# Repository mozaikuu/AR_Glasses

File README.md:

# Smart Glasses Distilled

This workspace was reorganized into a clean, role-based layout focused on a single Python backend and multiple client integrations.

## Folder Structure

```text
.
├── app/                # Core Python application
│   ├── api/            # HTTP and websocket endpoints
│   ├── agent/          # LLM orchestration and reasoning loop
│   ├── tools/          # Tool integrations (vision/search/navigation/speech)
│   ├── services/       # Runtime services (ASR/TTS/session/routing)
│   ├── models/         # Request/response and domain models
│   ├── config/         # Settings and environment config
│   └── shared/         # Shared helpers
├── bus_system/         # Isolated Smart Bus Tracking MVP workspace
├── clients/            # External client adapters/projects
│   ├── unity/          # Unity/HoloLens integration assets
│   ├── esp32/          # ESP firmware integration notes/assets
│   ├── mobile/         # Mobile client integration
│   └── browser/        # Browser/web integration
├── docs/               # Product and technical documentation
├── scripts/            # Utility scripts for setup/dev/ops
├── tests/              # Automated and smoke tests
├── assets/             # Static assets and models
└── archive/            # Legacy or deprecated snapshots
```

## Startup Contract

- Keep one launcher at project root: `start.py`.
- Core runtime code should live under `app/`.
- Clients should consume APIs only (no direct imports from internal modules).

## Bus System Workspace

All Smart Bus Tracking MVP modules are grouped under `bus_system/` for easier access:

- `bus_system/backend/` API and simulation runtime integration
- `bus_system/frontend/` Next.js dashboard and PWA
- `bus_system/simulation/` route and prediction modules
- `bus_system/agent_tools/` Cerebro tool wrappers
- `bus_system/docs/bus_tracking_mvp/` MVP docs

## Next Move

Place your current backend files under `app/` by responsibility (api/agent/tools/services/etc.), then update imports to use package paths from `app`.

---

Copyright © 2026 Ahmed Moussa

This software is provided to New Mansoura University solely for academic evaluation purposes.

No license, ownership rights, distribution rights, modification rights, or commercial rights are granted.

All intellectual property rights remain with the author.

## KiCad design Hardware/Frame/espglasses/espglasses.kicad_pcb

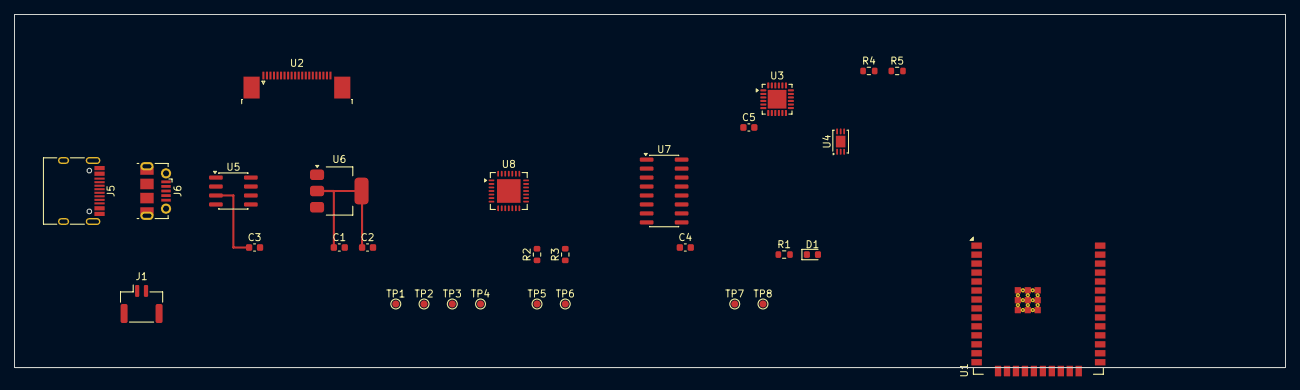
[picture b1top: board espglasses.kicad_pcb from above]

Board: 2 copper layers, 180.0 x 50.0 mm, 30 parts (0 on the bottom side), 15 nets.

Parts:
C1, C3: 10uF; C_0603_1608Metric
C2, C4, C5: 100nF; C_0603_1608Metric
D1: GREEN; LED_0603_1608Metric
J1: BATTERY_1S; JST_GH_SM02B-GHS-TB_1x02-1MP_P1.25mm_Horizontal
J5: USBC_POWER_IN; USB_C_Receptacle_HRO_TYPE-C-31-M-12
J6: MICRO_USB_PROG; USB_Micro-B_Molex-105017-0001
R1: 1k; R_0603_1608Metric
R2, R3, R4, R5: 10k; R_0603_1608Metric
TP1: TP_UART_TX; TestPoint_Pad_D1.0mm
TP2: TP_UART_RX; TestPoint_Pad_D1.0mm
TP3: TP_EN; TestPoint_Pad_D1.0mm
TP4: TP_IO0; TestPoint_Pad_D1.0mm
TP5: TP_I2C_SCL; TestPoint_Pad_D1.0mm
TP6: TP_I2C_SDA; TestPoint_Pad_D1.0mm
TP7: TP_SPK_P; TestPoint_Pad_D1.0mm
TP8: TP_SPK_N; TestPoint_Pad_D1.0mm
U1: ESP32_WROVER_E_CORE; ESP32-WROOM-32E
U2: OV2640_CAMERA_IF; TE_2-1734839-0_1x20-1MP_P0.5mm_Horizontal
U3: MPU6050_CORE; QFN-24-1EP_4x4mm_P0.5mm_EP2.65x2.65mm
U4: INMP441_CORE; DFN-6-1EP_3x2mm_P0.5mm_EP1.65x1.35mm
U5: LIION_CHARGER_IC_CORE; SOIC-8_3.9x4.9mm_P1.27mm
U6: REGULATOR_3V3_CORE; SOT-223-3_TabPin2
U7: AUDIO_AMP_CORE; SOIC-16_3.9x9.9mm_P1.27mm
U8: USB_UART_BRIDGE_CORE; QFN-28-1EP_5x5mm_P0.5mm_EP3.35x3.35mm

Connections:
+3V3_DIG: C1.1, C2.1, R2.1, R3.1, R4.1, R5.1, U1.2, U6.2, U8.9
EN: R4.2, TP3.1, U1.6, U8.7
GND: C1.2, C2.2, C3.2, D1.1, J1.2, J5.A1, J5.A12, J5.B1, J5.B12, J6.5, J6.6, U1.1, U5.4, U6.3, U8.2, U8.10
I2C_SCL: R2.2, TP5.1, U1.32
I2C_SDA: R3.2, TP6.1, U1.34
IO0: R5.2, TP4.1, U1.4, U8.8
LED_A: D1.2, R1.2
LED_STAT: R1.1, U1.8
UART_RX_DBG: TP2.1, U1.12, U8.5
UART_TX_DBG: TP1.1, U1.10, U8.6
USB_PROG_D+: J6.3, U8.3
USB_PROG_D-: J6.2, U8.4
VBAT_RAW: J1.1, U5.2
VBUS_5V: J5.A4, J5.A9, J5.B4, J5.B9, J6.1, U5.1, U8.1
VSYS: C3.1, U5.3, U6.1

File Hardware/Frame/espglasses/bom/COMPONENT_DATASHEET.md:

# Component Datasheet (Initial Concrete Set)

This file is generated from the concrete purchased-part implementation model.
Entries are the individual component-level building blocks for Rev-B decomposition.

| Ref | Part | Package | Role | Rail/Signal | Notes |
|---|---|---|---|---|---|
| U1 | ESP32-WROVER-E | Module | Main MCU + Wi-Fi/BLE | +3V3_DIG | Camera-capable ESP32 core |
| U2 | OV2640 | Camera sensor module/FFC | Image sensor | CAM_* | Parallel camera interface block |
| U3 | MPU-6050 | QFN (module-equivalent support) | 6-axis IMU | I2C_* | I2C sensor |
| U4 | INMP441 | LGA | Digital MEMS microphone | I2S_* | I2S microphone |
| U5 | Li-ion charger IC (Type-C input) | SOP/QFN | Battery charging | VBUS_5V/VBAT_RAW | Equivalent of purchased Type-C charger board |
| U6 | 3.3V regulator IC | SOT-223/SOT-23-5 | System regulation | VSYS/+3V3_DIG | Equivalent of purchased regulator stage |
| U7 | Audio amplifier IC | SOP/QFN | Speaker drive | AUD_IN/SPK_OUT | For 8 ohm 0.5W speaker |
| J1 | Li-ion battery connector | 2-pin JST | Battery input | VBAT_RAW | 3.7V 1000mAh battery |
| J2 | OLED panel connector | 4-pin header/FFC | Display interface | I2C_SCL/I2C_SDA | 1.3 inch I2C OLED |
| J3 | Camera connector | FFC/header | Camera link | CAM_* | OV2640 connection |
| J4 | Speaker connector | 2-pin | Audio transducer output | SPK_OUT | 20mm 8 ohm speaker |
| J5 | UART/boot header | 1x6 2.54mm | Debug/programming | UART/EN/IO0 | Bring-up and flashing |
| D1 | Status LED | 0603 | Power/status indication | LED_STAT | User-visible status |
| R1 | 1k | 0603 | LED current limit | LED_STAT | Status LED resistor |
| R2 | 10k | 0603 | I2C pull-up | I2C_SCL | Bus pull-up |
| R3 | 10k | 0603 | I2C pull-up | I2C_SDA | Bus pull-up |
| R4 | 10k | 0603 | EN pull-up | EN | ESP32 enable strap |
| R5 | 10k | 0603 | IO0 pull-up | IO0 | ESP32 boot strap |
| C1 | 10uF | 0603/0805 | Bulk decoupling | +3V3_DIG | Near ESP32/regulator |
| C2 | 100nF | 0603 | HF decoupling | +3V3_DIG | Near ESP32 power pins |
| C3 | 10uF | 0603/0805 | Regulator output bulk | +3V3_DIG | Regulator stability |
| C4 | 100nF | 0603 | Mic decoupling | +3V3_AUD | Near INMP441 |
| C5 | 100nF | 0603 | IMU decoupling | +3V3_DIG | Near MPU-6050 |
| X1 | HW-104 (exact variant pending) | Unknown | Unresolved purchased module | TBD | Needs exact module identification before schematic lock |

## Notes

- HW-104 is intentionally marked unresolved until exact module function is confirmed.
- Final manufacturer part numbers and exact footprints should be locked before fabrication.
- This file is intended to be updated as schematic references are finalized.

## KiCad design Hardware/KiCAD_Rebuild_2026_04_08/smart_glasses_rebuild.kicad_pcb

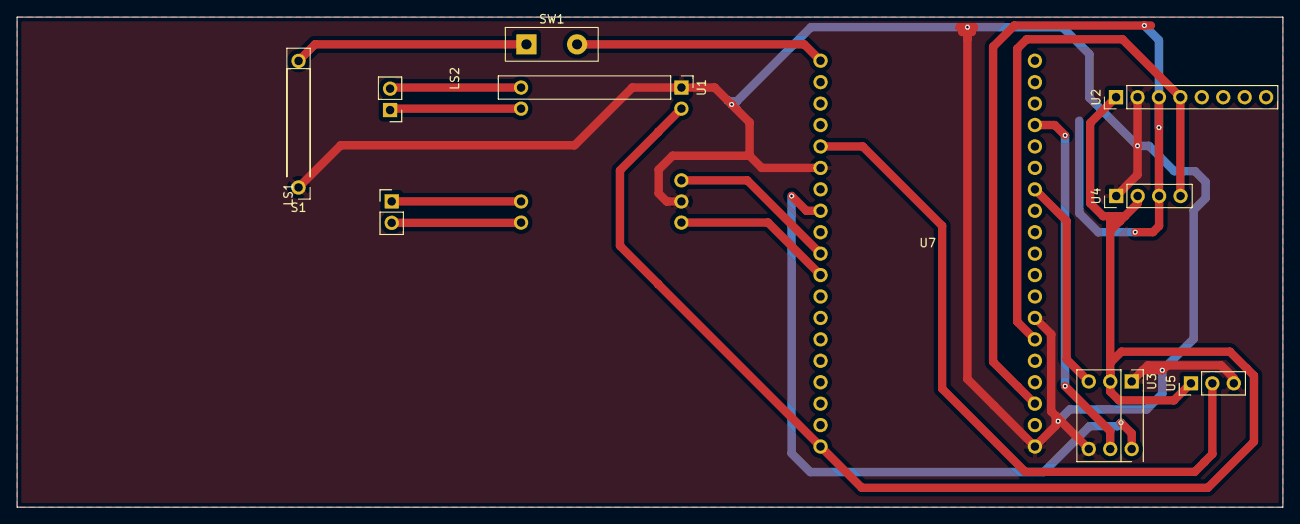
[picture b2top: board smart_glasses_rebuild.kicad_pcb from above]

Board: 2 copper layers, 150.0 x 58.1 mm, 10 parts (0 on the bottom side), 16 nets.

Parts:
LS1, LS2: Small Speaker; PinHeader_1x02_P2.54mm_Vertical
S1: TP4056_BMS; PinHeader_1x06_P2.54mm_Vertical
SW1: PWR_SW_LATCH; Power_Switch_Latching_SPST_2Pin
U1: HW-104; PinHeader_1x09_P2.54mm_Vertical
U2: MPU-6050_Breakout; PinHeader_1x08_P2.54mm_Vertical
U3: INMP441; PinHeader_1x06_P2.54mm_Vertical
U4: IIC_OLED; PinHeader_1x04_P2.54mm_Vertical
U5: HW-763; PinHeader_1x03_P2.54mm_Vertical
U7: ESP32-WROVER-dev; ESP32_WROVER_DEV_2x19_WIDE

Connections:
GND: S1.6 (OUT-), U1.1 (GND), U1.4 (SIG_GND), U2.2 (GND), U3.1 (GND), U3.6 (L/R), U4.1 (GND), U5.3 (GND), U7.14 (GND), U7.20 (GND), U7.26 (GND)
unnamed: LS1.1 (+), U1.8 (R+)
unnamed: LS1.2 (-), U1.9 (R-)
unnamed: LS2.1 (+), U1.6 (L+)
unnamed: LS2.2 (-), U1.7 (L-)
unnamed: S1.5 (OUT+), SW1.1
unnamed: U1.5 (LIN), U7.9 (GPIO25)
unnamed: U1.3 (RIN), U7.10 (GPIO26)
unnamed: U1.2 (VCC), U2.1 (VCC), U3.2 (VDD), U4.2 (VCC), U5.1 (VCC), U7.1 (3V3)
unnamed: U2.3 (SCL), U4.3 (SCL), U7.22 (GPIO22)
unnamed: U2.4 (SDA), U4.4 (SDA), U7.25 (GPIO21)
unnamed: U3.4 (SCK), U7.12 (GPIO14)
unnamed: U3.3 (SD), U7.32 (GPIO4)
unnamed: U3.5 (WS), U7.35 (GPIO15)
unnamed: U5.2 (SIG), U7.15 (GPIO13)
unnamed: SW1.2, U7.19 (5V)

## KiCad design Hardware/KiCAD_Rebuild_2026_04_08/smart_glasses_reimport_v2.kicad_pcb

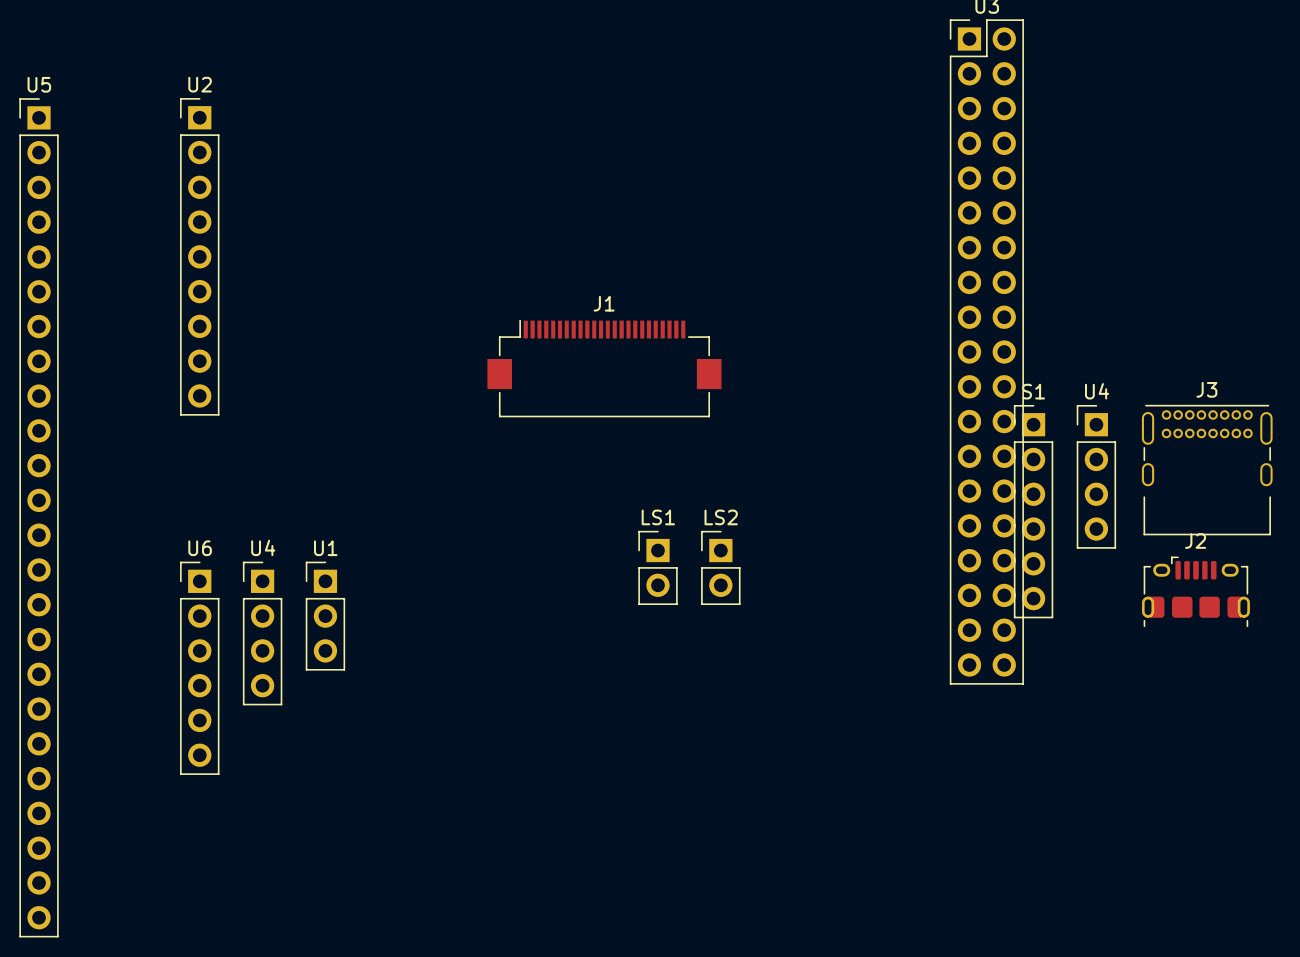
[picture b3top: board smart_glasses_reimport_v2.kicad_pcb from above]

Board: 2 copper layers, 13 parts (0 on the bottom side), 7 nets, no tracks yet.

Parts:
J1: OV2640_STRIP_CONN; Hirose_FH12-24S-0.5SH_1x24-1MP_P0.50mm_Horizontal
J2: DEBUG_USB_MICRO; USB_Micro-B_Amphenol_10118194_Horizontal
J3: CHARGE_USB_C; USB_C_Receptacle_GCT_USB4085
LS1, LS2: Small Speaker; PinHeader_1x02_P2.54mm_Vertical
S1: TP4056_BMS; PinHeader_1x06_P2.54mm_Vertical
U1: HW-763; PinHeader_1x03_P2.54mm_Vertical
U2: HW-104; PinHeader_1x09_P2.54mm_Vertical
U3: ESP32-WROVER-dev; PinHeader_2x19_P2.54mm_Vertical
U4: IIC OLED; PinHeader_1x04_P2.54mm_Vertical
U4#2: HW-764_5V_to_3V3; PinHeader_1x04_P2.54mm_Vertical
U5: OV2640; PinHeader_1x24_P2.54mm_Vertical
U6: INMP441; PinHeader_1x06_P2.54mm_Vertical

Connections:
/CAM_1: J2.5 (GND), U1.2 (GND), U2.5 (SIG_GND), U3.6 (GPIO35), U3.32 (GPIO4), U3.38 (SD_CLK/GPIO6), U4.2 (GND), U4#2.2 (IN-), U4#2.4 (OUT-), U6.4 (WS)
/CAM_8: U3.33 (GPIO0), U4.4 (SDA)
/CAM_12: J1.12 (Y4), U3.17 (SD_DATA_3/GPIO10)
/CAM_16: U3.26 (GND), U6.5 (SD)
/MIC_WS: U3.23 (U0TXD/GPIO1), U6.6 (L/R)
/SPK_RN: LS2.1 (+), U2.9 (R-)
/TOUCH_SIG: U1.3 (SIG), U3.5 (GPIO34)

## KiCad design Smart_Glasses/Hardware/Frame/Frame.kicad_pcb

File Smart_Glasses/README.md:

# Smart Glasses Project

Your AI companion and navigation in Smart Glasses - A multimodal LLM agent with vision, voice, and text capabilities.

## Repo Index

See `docs/PROJECT_INDEX.md` for a map of all sub-projects in this monorepo (Python agent/UI/server, Unity HoloLens project, firmware, mobile, and prototypes).

## Project Structure

The project follows a domain-driven architecture:

```
Smart_Glasses/
├── ui/                    # Streamlit frontend
│   ├── app.py            # Main Streamlit app
│   ├── components/       # UI components
│   └── utils/            # UI utilities
├── agent/                # LLM agent logic
│   ├── llm.py           # LLM model handling & generation
│   ├── agent_loop.py    # Main agent reasoning loop
│   └── modes.py         # Quick/thinking mode logic
├── tools/                # MCP tools
│   ├── vision/          # Computer vision tools (YOLO)
│   ├── search/          # Web search tools
│   ├── speech/          # Speech recognition & TTS
│   └── navigation/      # GPS/navigation tools
├── server/               # MCP server
│   ├── server.py        # FastMCP server definition
│   └── gateway.py       # HTTP gateway for Streamlit
├── models/               # Data models
│   └── requests.py      # Pydantic models for API
├── config/               # Configuration
│   ├── settings.py      # App settings
│   └── model_config.py  # LLM model configuration
└── shared/               # Shared utilities
    └── utils.py         # Common utilities
```

## Features

-  **Multimodal Input**: Support for text, voice, and image inputs
-  **Two Agent Modes**:
   -  **Quick Mode**: Fast single-pass responses
   -  **Thinking Mode**: Deep reasoning with history looping until satisfied
-  **MCP Tools**:
   -  `VisionDetect`: Real-time object detection using camera and YOLO model
   -  `search_web`: Web search and context retrieval
-  **Streamlit UI**: Interactive web interface with live camera and audio capture

## Quickstart

### 1. Install Dependencies

**Important**: You must install dependencies before running the application!

**Option A: Using `uv` (Recommended)**

```bash
uv sync
```

**Option B: Using `pip`**

```bash
pip install -r requirements.txt
```

### 2. Activate Virtual Environment

**Windows:**

```bash
.venv\Scripts\activate
```

**Linux/Mac:**

```bash
source .venv/bin/activate
```

### 3. Start the HTTP Gateway

**Open a terminal** (with venv activated) and run:

**Windows (using batch file):**

```bash
start_gateway.bat
```

**Linux/Mac (using shell script):**

```bash
chmod +x start_gateway.sh
./start_gateway.sh
```

**Or manually:**

```bash
python start_gateway.py
```

You should see:

```
🚀 Starting gateway server on localhost:8000
INFO:     Uvicorn running on http://localhost:8000
```

**⚠️ Keep this terminal open!** The gateway must be running for the Streamlit app to work.

The gateway will be available at `http://localhost:8000`

### 4. Start the Streamlit App

**Open a NEW terminal**, activate the virtual environment, and run:

**Windows (using batch file):**

```bash
start_streamlit.bat
```

**Linux/Mac (using shell script):**

```bash
chmod +x start_streamlit.sh
./start_streamlit.sh
```

**Or manually:**

```bash
# Activate venv first
streamlit run ui/app.py
```

The app will open in your browser at `http://localhost:8501`

### Troubleshooting

**"ModuleNotFoundError" or "No module named 'fastapi'"**

-  Solution: Install dependencies first with `uv sync` or `pip install -r requirements.txt`

**"Connection refused" or "Gateway Offline"**

-  Solution: Make sure the gateway server is running (Step 2). Check that you see the startup message in the gateway terminal.

See `QUICKSTART.md` for more detailed troubleshooting.

## Usage

1. **Text Input**: Type your question in the text area
2. **Image Input**: Click "Capture Frame" to capture the current camera frame
3. **Voice Input**: Click "Capture Audio" to capture audio from your microphone
4. **Send Request**: Click "Send Request" to process all inputs together
5. **Mode Selection**: Choose between "quick" (fast) or "thinking" (deep reasoning) mode

The agent will:

-  Transcribe audio if provided
-  Combine text + transcribed audio + image into a unified prompt
-  Process through the LLM agent with available MCP tools
-  Return a response

## Configuration

Edit `config/settings.py` or set environment variables:

-  `MODEL_ID`: LLM model identifier (default: "google/gemma-3-4b-it")
-  `DEVICE`: "cuda" or "cpu" (default: auto-detected)
-  `API_HOST`: Gateway host (default: "localhost")
-  `API_PORT`: Gateway port (default: 8000)
-  `MAX_LOOPS`: Maximum agent loop iterations (default: 8)

## MCP Server

The MCP server can be used independently with Claude Desktop or other MCP clients.

### Claude Desktop Configuration

On Windows: `%APPDATA%/Claude/claude_desktop_config.json`

```json
{
	"mcpServers": {
		"smart-glasses": {
			"command": "uv",
			"args": [
				"--directory",
				"D:\\0_code\\New_ideas\\1_Coding_Now\\Smart_Glasses",
				"run",
				"fastmcp",
				"run",
				"server.server:mcp",
				"--transport",
				"stdio"
			]
		}
	}
}
```

### Debugging with MCP Inspector

```bash
npx @modelcontextprotocol/inspector uv --directory D:\0_code\New_ideas\1_Coding_Now\Smart_Glasses run fastmcp run server.server:mcp --transport stdio
```

## Development

### Project Scripts

-  `start_gateway.py`: Start the HTTP gateway server
-  `server/server.py`: MCP server entry point
-  `ui/app.py`: Streamlit application

### Testing

Test the end-to-end flow:

1. Start the gateway
2. Start the Streamlit app
3. Try different input combinations (text, image, audio)
4. Test both quick and thinking modes
5. Verify MCP tool calls work (vision detection, web search)

## Migration Notes

See `MIGRATION_NOTES.md` for details about the refactoring from the old structure.

## Dependencies

Key dependencies:

-  `fastmcp`: MCP server framework
-  `streamlit`: Web UI framework
-  `streamlit-webrtc`: WebRTC for camera/audio
-  `transformers`: LLM models
-  `torch`: Deep learning framework
-  `ultralytics`: YOLO object detection
-  `whisper`: Speech recognition
-  `edge-tts`: Text-to-speech
-  `fastapi`: HTTP API framework

See `pyproject.toml` for the complete list.

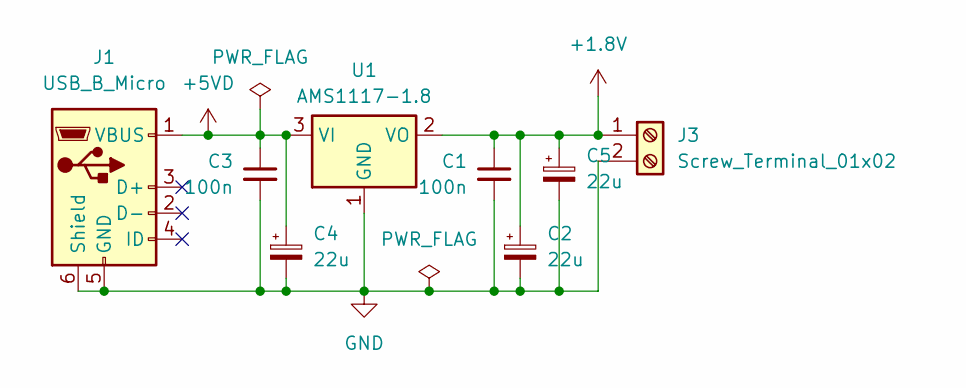
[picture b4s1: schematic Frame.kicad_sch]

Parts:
C1, C3: 100n; C_0402_1005Metric
C2, C4, C5: 22u; CP_Elec_6.3x7.7
J1: USB_B_Micro; USB_Micro-B_Amphenol_10118194_Horizontal
J3: Screw_Terminal_01x02; TerminalBlock_Phoenix_MKDS-1,5-2-5.08_1x02_P5.08mm_Horizont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
U1: AMS1117-1.8; SOT-223-3_TabPin2

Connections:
+1.8V: C1.1, C2.1, C5.1, J3.1, U1.2 (VO)
+5VD: C3.1, C4.1, J1.1 (VBUS), U1.3 (VI)
GND: C1.2, C2.2, C3.2, C4.2, C5.2, J1.5 (GND), J1.6 (Shield), J3.2, U1.1 (GND)

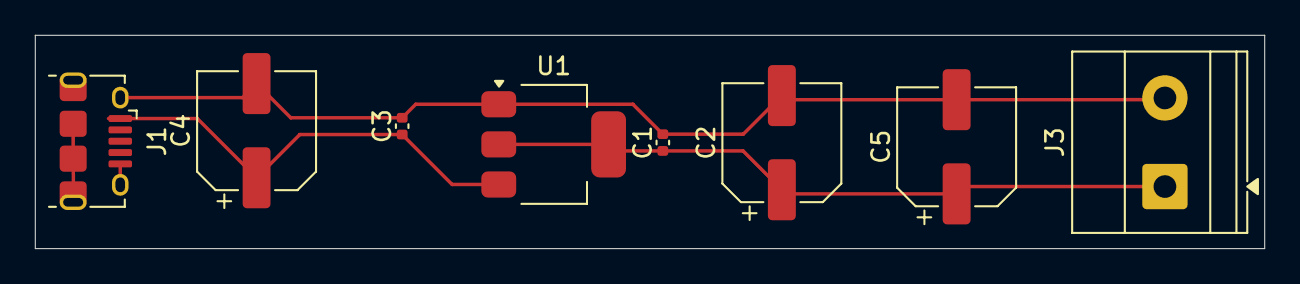
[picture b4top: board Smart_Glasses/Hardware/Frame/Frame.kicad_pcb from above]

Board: 2 copper layers, 70.5 x 12.2 mm, 8 parts (0 on the bottom side), 3 nets.

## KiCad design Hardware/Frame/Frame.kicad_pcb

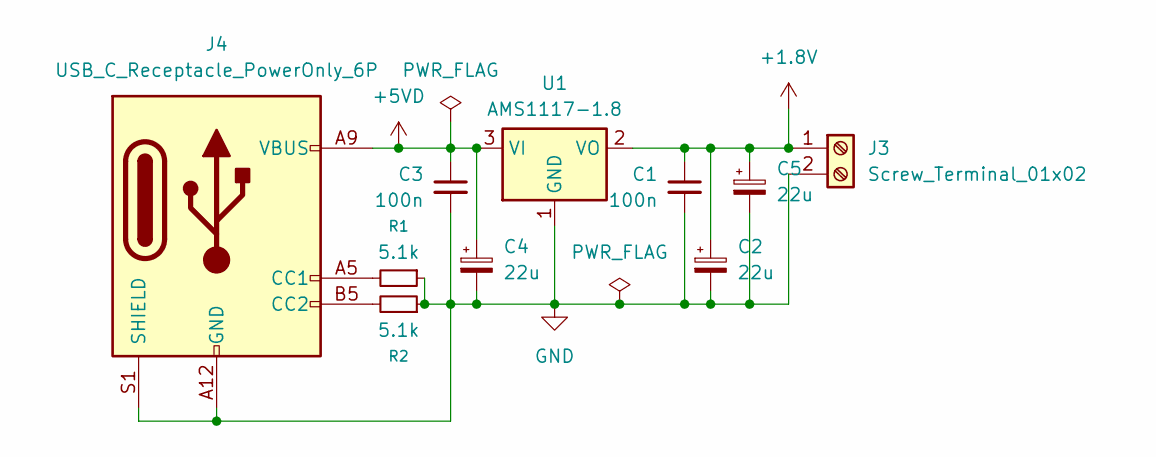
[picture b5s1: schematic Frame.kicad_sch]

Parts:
C1, C3: 100n; C_0402_1005Metric
C2, C4, C5: 22u; CP_Elec_6.3x7.7
J3: Screw_Terminal_01x02; TerminalBlock_Phoenix_MKDS-1,5-2-5.08_1x02_P5.08mm_Horizont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
J4: USB_C_Receptacle_PowerOnly_6P; USB_C_Receptacle_HRO_TYPE-C-31-M-12
R1, R2: 5.1k; R_0402_1005Metric
U1: AMS1117-1.8; SOT-223-3_TabPin2

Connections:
+1.8V: C1.1, C2.1, C5.1, J3.1, U1.2 (VO)
+5VD: C3.1, C4.1, J4.A9 (VBUS), J4.B9 (VBUS), U1.3 (VI)
GND: C1.2, C2.2, C3.2, C4.2, C5.2, J3.2, J4.A12 (GND), J4.B12 (GND), J4.S1 (SHIELD), R1.1, R2.1, U1.1 (GND)
unnamed: J4.A5 (CC1), R1.2
unnamed: J4.B5 (CC2), R2.2

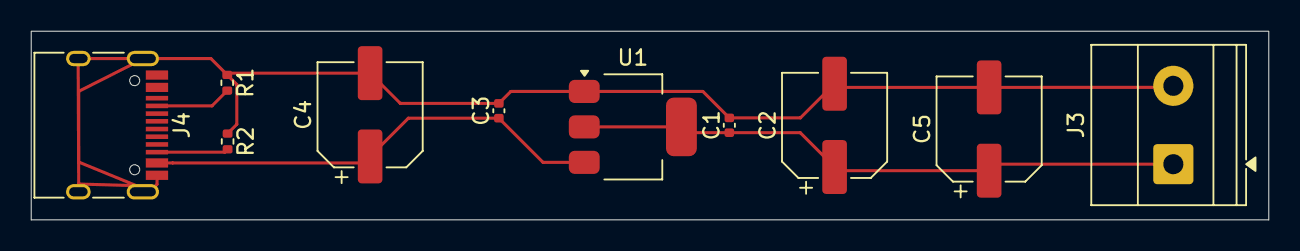
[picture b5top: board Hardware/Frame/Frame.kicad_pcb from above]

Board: 2 copper layers, 80.2 x 12.2 mm, 10 parts (0 on the bottom side), 5 nets.

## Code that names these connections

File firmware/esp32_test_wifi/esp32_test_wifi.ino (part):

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#define PROFILE_USE_TOUCH 1
#else
// Camera-priority default profile:
// WROVER camera pin map overlaps with SH1106 I2C (GPIO21/22) and DAC TTS (GPIO25/26).
// Camera D0 also uses GPIO4, which conflicts with the I2S mic data pin.
// Keep camera enabled and disable conflicting peripherals in the default profile.
#define PROFILE_USE_SH1106 0
#define PROFILE_USE_DAC_TTS 0
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#else
#define TOUCH_PAD_PIN 18
#endif
#define I2C_SDA_PIN 21
#define I2C_SCL_PIN 22
#define I2S_MIC_BCK 14
#define I2S_MIC_WS 15
#define I2S_MIC_DATA 4
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
#if USE_TOUCH
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#error "TOUCH_PAD_PIN conflicts with camera pins. Move touch OUT to a camera-safe GPIO (e.g. GPIO13)."
#endif
#endif
#endif
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  pinMode(DAC_TTS_LEFT_PIN, OUTPUT);
  pinMode(DAC_TTS_RIGHT_PIN, OUTPUT);
  writeDacPair(128);
  Serial.println("TTS DAC init on GPIO25/26");
}

bool playWavFromHttp(HTTPClient &http)
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  i2s_zero_dma_buffer(I2S_NUM_0);
  micDriverInstalled = true;
  micReady = true;
  Serial.println("I2S mic ready (GPIO14/15/4)");
#else
  micReady = false;
#endif
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  pinMode(TOUCH_PAD_PIN, INPUT_PULLDOWN);
#endif
#if USE_SH1106
  Wire.begin(I2C_SDA_PIN, I2C_SCL_PIN);
#endif

#if USE_SH1106
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
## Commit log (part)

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2025-10-15 Init Unity Template
2025-10-15 Init Unity Start Ready
2025-10-16 Surprise update
2025-10-16 mouse movement
2025-10-17 exit btn
2025-10-18 Collision detection
2025-10-20 addtional edits
2025-10-20 test
2025-10-20 menu esc
2025-10-22 sounds&url
2025-10-22 flasks import with collision
2025-10-23 Misc
2025-10-23 Hard_Reset
2025-10-23 Both_input_Systems
2025-10-24 Fixing Version Control
2025-10-24 new collision test
2025-10-24 added Other Scenes
2025-10-24 FIxed Some Errors
2025-10-28 reactions
2025-11-07 Adding ClassElement
2025-11-18 Change Of Plans...
2025-11-18 TTP Done. for now
2025-11-19 Better test case and file structure
2025-11-20 BMC + Comp_analysis + Presentation
2025-11-21 An attempt at GPS facing position without the needed modules
2025-12-01 Added Documentation stuff+ Project vision + GPS
2025-12-01 VC Fix
2025-12-01 Test GPS Done
2025-12-02 Panic at the disco
2025-12-02 Changed folder structur to start MCP Server
2025-12-02 MCP WIP
2025-12-03 Folder Restructure... again
2025-12-20 lots of stuff mainly client llm server stuff. kept forgetting to push so consider this a snapshot with alot of changes in physical files inside (old) plus other updates known to work separately. bad 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
2025-12-20 latest and greatest
2025-12-26 broken stuff but a snapshot none the less
2026-01-08 Audio works now. the start of vibe coding and i hate it
2026-01-11 nova wake up
2026-01-11 Nova + gui
2026-01-16 prep next task
2026-01-16 Fix Version Control
2026-01-16 Team meeting
2026-01-16 move repo + todo upd
2026-01-16 req fix
2026-01-16 streamlit online fix?
2026-01-16 streamlit misbehavior
2026-01-17 sl hotfix
2026-01-20 presentation prep
2026-01-27 updated and cleaned todo + might add moltbot to the repo.
2026-01-28 added 3 month plan in todo
2026-01-28 Nav start
2026-01-30 Claude Code Massacre
2026-01-30 nav integrated
2026-02-01 broken
2026-02-01 Todo to see how gh works
2026-02-01 Rapture + fix code
2026-02-01 requirements?
2026-02-01 fixed mot errors
2026-02-01 build: replace ddgs with duckduckgo-search package
    Update pyproject.toml and check_dependencies.py to use the duckduckgo-search package instead of ddgs. This change aligns with the package naming used in the import statements and ensures consistency 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
2026-02-02 feat(wakeword): add pause/resume and device selection
    - Add pause() and resume() methods to temporarily stop/restart wake word detection
    - Add device_index parameter to allow specifying audio input device
    - Implement auto-refresh loop in Streamlit app for background event processing
    - Add audio device discovery function to find valid input devices
    - Ensure wake word system resumes after manual audio recording
2026-02-02 Streamlit -> Flask
2026-02-02 wakeword fixed
2026-02-02 feat(services): auto-start wake word listening and improve vision tool
    - WakeWordService now automatically starts listening on initialization
    - Update vision model path and add automatic download fallback
    - Expand vision tool trigger phrases for more natural queries
    - Fix camera error message with correct model path reference
2026-02-02 downloaded yolo models
2026-02-02 TTS Implementation
2026-02-05 todo++
2026-02-05 running website on phone
2026-02-05 hotfix
2026-02-07 Update Todo.md
    removed some finished stuff
2026-02-08 moondream hotfix
2026-02-09 qrcodes + Nav implementation start
2026-02-10 added a script to run all scripts at once + fixing phone webapp
2026-02-10 fixing agent overthinking
2026-02-12 Unity integration + broken code
2026-02-12 project rework from the grave + codex
2026-02-12 Backend Checkpoint
2026-02-12 Everything-refixed
2026-02-12 fixed tool calling - broken-ish search tool
2026-02-14 Unity Integration
2026-02-20 Made a regulator in kicad
2026-02-20 Implement TTS interrupt support
    Added support for interrupting text-to-speech playback using a global stop flag.
2026-02-20 Refactor audio processor and update UI elements
2026-02-20 Refactor audio processing and update UI title
    Updated the UI title and modified audio processing logic to include speech-to-text functionality. Changed API endpoint variable name and adjusted webrtc_streamer key.
2026-02-22 ar-nav-multiset Integration
2026-02-26 Hardware Changes
2026-02-27 added glasses functionality.
2026-02-27 phone works
2026-02-27 Checkpoint. Radical changes next push
2026-03-01 ESP32 Works WIFI & BLE
2026-03-01 esp works on god frfr
2026-03-01 added esp oled scrolling
2026-03-01 HARDWARE 95% DONE
2026-03-02 radical changes incoming
2026-03-07 Hololens Development Done -Tweaks
2026-03-12 Prepared ai Nav
2026-03-12 hololens mega plan
2026-03-18 hololens 2 aftercheckpoint.
2026-03-19 meta quest popup menu integrated
2026-03-19 fixed scene
2026-03-21 refactor prep. Checkpoint
2026-03-21 cleanup + ArchReplan for refactoring
2026-03-21 cleanup + Arch docs +refactor prep
2026-03-23 esp recovered + server refactored
2026-03-23 Unity recovered
2026-03-23 todo?
2026-03-23 repo old code incineration
2026-03-23 unity tweaks
2026-03-23 Production Preparation
2026-03-24 kicad start
2026-03-24 kicad checkpoint
2026-03-24 kicad checkpoint 2
2026-03-24 kicad source of truth
2026-03-26 ide crashed mid response...
2026-03-28 refactor
2026-03-29 checkpoint
2026-03-29 unit tests
2026-03-29 grad prep
2026-03-29 Presentations
2026-04-02 platformio. esp32 mic works.
2026-04-02 midpoint esp cam
2026-04-02 mega fork to MVP
2026-04-04 MVP Breakdown should have been a new branch
2026-04-04 firmware: camera-priority default profile for ESP flash
2026-04-04 Intermediary
2026-04-10 kicad checkpoint new approach
2026-04-11 kicad manual checkpoint
2026-04-11 kicad almost done
2026-04-13 kicad adding button for pwr
2026-04-13 Kicap Prototype 2 done
2026-04-13 prototype ready for printing
2026-04-23 Checkpoint. dont remember if broken plus added bus system pretest
2026-04-23 finance
2026-04-25 METAXR
2026-05-01 prep for mobile
2026-05-01 phone template established
2026-05-01 bus system mid point.
2026-05-01 bus path
2026-05-01 real time bus tracking
2026-05-01 track saving and mobile lag fix
2026-05-02 bus.tsh done. starting companion.
2026-05-02 Companion 90% done. moondream unavailable
2026-05-03 tried to fix moondream. still broken.
2026-05-03 docs
2026-05-03 Home + indoor nav tabs almost done
2026-05-03 testing multiple indoor nav types
2026-05-05 trying to fix lidar again...
2026-05-05 usable 2d navigation model
2026-05-13 Checkpoint Docs
2026-05-13 removed videos
2026-06-20 creating a paper trail
